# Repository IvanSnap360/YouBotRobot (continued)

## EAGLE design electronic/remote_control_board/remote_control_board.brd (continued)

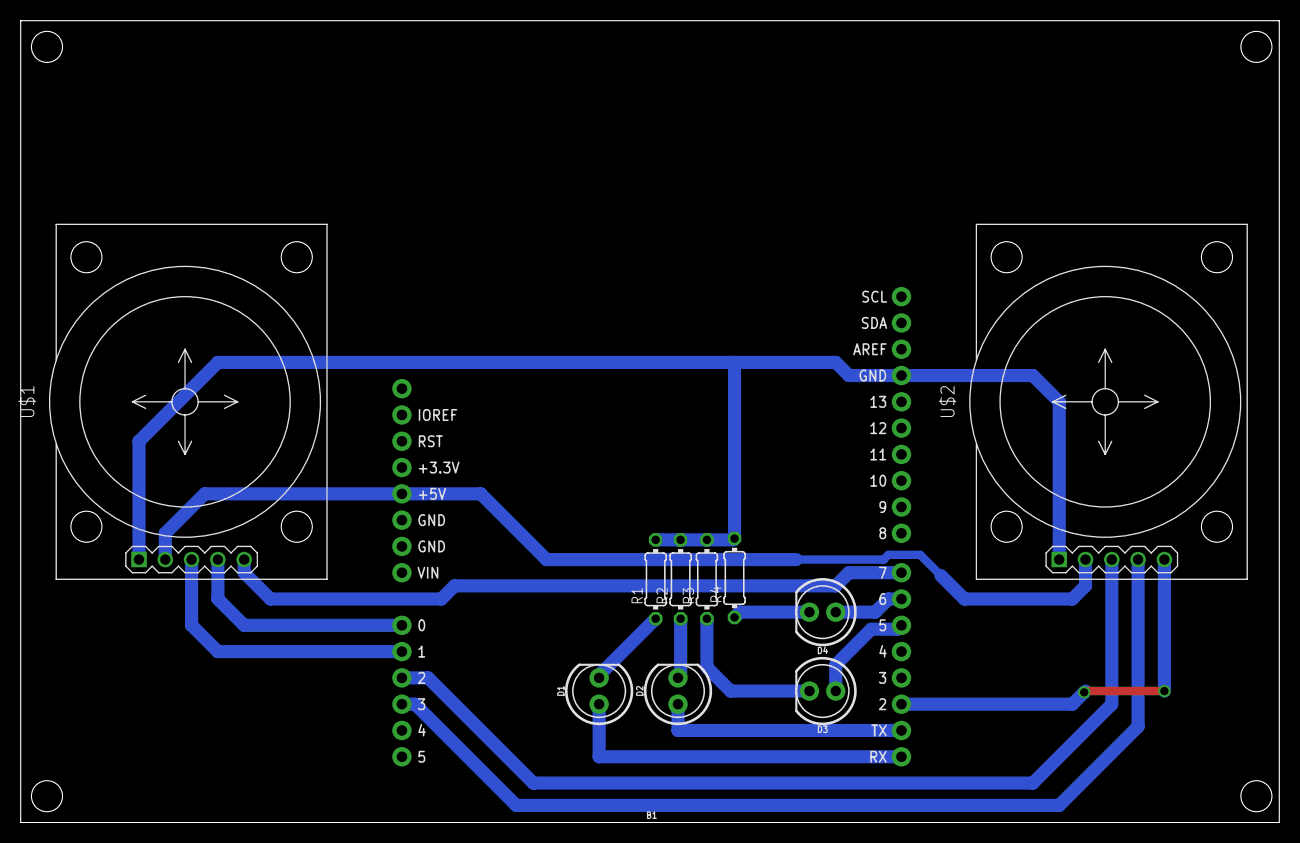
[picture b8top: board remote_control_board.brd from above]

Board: 2 copper layers, 121.6 x 77.5 mm, 11 parts (0 on the bottom side), 16 nets.

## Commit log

2021-09-17 add readme
2021-10-02 add test
2021-10-02 add test description
2021-10-02 add simple driver
2021-10-02 add teleop
2021-10-02 add raw test firmware
2021-10-02 add test platform firmware
2021-10-03 add realsenses lib, add some launch files
2021-10-03 add simple manipulator package and moveit package
2021-10-04 some fix
2021-10-11 fix bugs
2021-10-18 some fixes
2021-10-18 add remote controller
2021-10-19 fix bugs, add joystic, add occupancy
2021-10-24 change navigation package
2021-10-24 change manipulator moveit package
2021-10-25 add rosbag launch, change params
2021-10-26 soe fix
2021-11-02 fix manipulator moveit package
2021-11-02 syns_from_roboPC
2021-11-02 SYNS_FROM_ROBOT_PC
2021-11-03 driver fix
2021-11-04 add DWB and PythonRosConverters
2021-11-04 {test commit}
2021-11-04 test
2021-11-04 add robot_description and test moveit package
2021-11-06 remake omnibot moveit pkg, but not working
2022-01-14 add remote_control_board
2022-03-06 add raft simulator
2022-03-06 add new model
2022-03-07 add gazebo model
2022-03-08 add gazebo sim with controllers
2022-11-04 start new branch
2022-12-06 add own manipulator
2022-12-11 remove big files
2022-12-18 fix paths
2022-12-20 manipulator and specs
    finish manipulator and add raw specs
    next is create a gripper
2022-12-23 add new pcb versions
2022-12-26 add sim models
2022-12-26 change src
2022-12-27 add first version of platform description
2022-12-28 add raw package graph
2023-01-02 commit for linux test
2023-01-06 add rtabmap first edition
2023-01-06 add controllers
2023-01-08 change mecanum wheel model
2023-01-15 add teleop pkg
2023-01-15 some fixes in gazebo pkg
2023-01-15 fix bugs in joints
2023-01-15 teleop bugs fix
2023-01-17 add occupancy pkg
2023-02-11 fix odom bugs, add sensor odom manager package
2023-02-11 omnibot_navigation -> omnibot_platform_navigation
2023-02-12 combine manipulator and platform packages
2023-02-12 fix sync manipulator movements gazebo and rviz bug
2023-02-12 add move_base to navigation pkg
2023-02-13 some clean
2023-02-15 cosmetical edit
2023-02-15 cosmetic 2
2023-02-17 fix connection bug in joint state
2023-02-17 fix platform teleop bug
2023-02-17 cosmetic
2023-02-18 add manipulator moveit package
2023-02-24 save before changing manipulator description
2023-02-26 fix worlds bug
2023-03-08 add firmware V3, change planners params
2023-03-09 some model changes
2023-03-10 add battry controller test firmware
2023-03-20 fix bugs controller_firmare, add battery manager
2023-03-20 add set pid koef function to actuator lib
2023-03-21 fix bugs in battery manager pkg
2023-03-30 add localization arg ro launch file
2023-04-01 add omnibot_firmware_V4_0
2023-04-02 some changes in omnibot_firmware_V4_0
2023-04-09 fix some packages visibility
2023-04-10 changes in actuator pid
2023-04-11 add low level controller connector, fix bugs
2023-04-14 bring develop myself manipulator controller
2023-04-23 add cooling system and power to manip
2023-04-27 fix launch files for real robot,delete rslib in ws
2023-04-29 some changes
2023-04-29 add teb planner additional plugins
2023-04-29 add gmapping for test
2023-04-30 add navigation package structure
2023-04-30 add new map, localization launch files and ex
2023-04-30 add manipulator moveit interface
2023-05-01 add manipulator control server
2023-05-02 save before change rtab for odometry
2023-05-05 new costmap params
2023-05-05 add new_maps
2023-05-06 save before change manipulator moveit package
2023-05-11 save before rtabmap launch rewrite
2023-05-15 add localization, add start of web page
2023-05-16 kv33_map_edit
2023-05-16 web changes
2023-05-16 navigation package stucture optimization
2023-05-17 some chages
2023-05-18 save before rtabmap change
2023-05-19 edit rtabmap and move_base config
2023-05-25 some changes in web package
2023-05-27 chanes in navigation
2023-05-28 fix git bug
2023-05-28 deleting before repearing
2023-05-28 deleting2
2023-05-28 restore
2023-05-29 fix serial output
    fix serial output in battery controller firmware
2023-05-29 pins setup bug fix
2023-05-30 good params for teb planner
2023-06-01 fix teb local planner linear y bug
2023-06-02 add state machine
2023-06-02 real and rtabamp configs change
2023-06-03 change battery controller firmware
2023-06-03 some rtabmap changes
2023-06-04 some changes in rtabmap launch file
2023-06-05 att d435 to manipulator
2023-06-09 real manipulator works with moveit
2023-06-09 add sim switcher
2023-06-09 copy trajectory retraslator to server (manip)
2023-06-10 add omnibot_core startup actions
2023-06-10 some changes on manipulator packages
2023-06-10 change in startup launch files
2023-06-10 action server fix
2023-06-10 fix battery controller firmware
2023-06-10 add pointcloud relay node with control service
2023-06-13 add aruco cubes spawner
2023-06-13 bug fix in action_server_lib
2023-06-14 setup new hw controller
2024-06-30 fix readme
2024-08-12 add motor drivers. orangepi, new body
2024-08-22 add battery module
2024-08-25 add manip, realseses, fix battery module
2024-08-26 add models for ros
2024-09-05 add edited dae model
2024-09-08 add platform base description package and launch file
2024-09-08 add slamtech rplidar A3 3d-model and urdf model
2024-09-08 add sensors positions sheme
2024-09-08 fix platform descr
2024-09-08 add joint state gui publisher
2024-09-08 add omnibot_description + launch file
2024-09-08 add bringup launch file
2024-09-12 add gazebo package launch file, setup bringup launch file ro sim, add worlds
2024-09-20 add rs_d435, add sim start script, fix gazebo launch file
2024-09-20 fix sim start, add to sim start rviz enablr param
2024-09-29 add t265
2024-10-06 add controllers and controller manager
2024-10-06 move platfrom controller to platform_package, add velocity example
2024-10-07 add omnibot_platform_control.launch sim arg
2024-12-29 fix assembly
2024-12-30 clean ros pkgs
2024-12-30 rewrite platfrom description
2024-12-31 add start comdition for gz_sim
2025-01-02 add lonk with gazebo and velocity controller
2025-01-02 add sync with rviz2 and gz
2025-01-02 omnibot_controllers config move to omnibot_platform_control
2025-01-03 add lidar
2025-01-05 add worlds, fix lidar "xray"
2025-01-19 add mecanum driver
2025-01-19 add node for translation to controllers
2025-01-19 fix not movin in gazebo
2025-01-19 fix some frictions issues
2025-01-19 turn off gazebo_gui
2025-01-26 add platform teleop package
2025-01-26 some fixes in urdf
